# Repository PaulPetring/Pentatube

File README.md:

# Pentatube

144 leds filled with a new life

## Ongoing Documentation:

https://hackmd.c3d2.de/Pentatube

## Schematics

| Part         | Description | Datasheet |
|:------ |:----------- |:----------|
| XCVR1, XCVR2 | Differential Bus Transceiver | [SN65176B](http://www.ti.com/lit/ds/symlink/sn75176b.pdf) |
| SRR, SRG, SRB | 8-Bit Shift Register with Latch and Driver | [TPIC6595](http://www.ti.com/lit/ds/symlink/tpic6595.pdf) |
| uC    | ATMEL 8-Bit Microncontroller | [AT89C2051-24PU](https://ww1.microchip.com/downloads/en/DeviceDoc/doc0368.pdf) |
| MYC  | (probably) RGB LED  driver with PWM control. marked: JRC 6060 523 | [NJU6060](https://www.mouser.de/datasheet/2/294/NJU6060_E-52910.pdf) |

## Controller

)

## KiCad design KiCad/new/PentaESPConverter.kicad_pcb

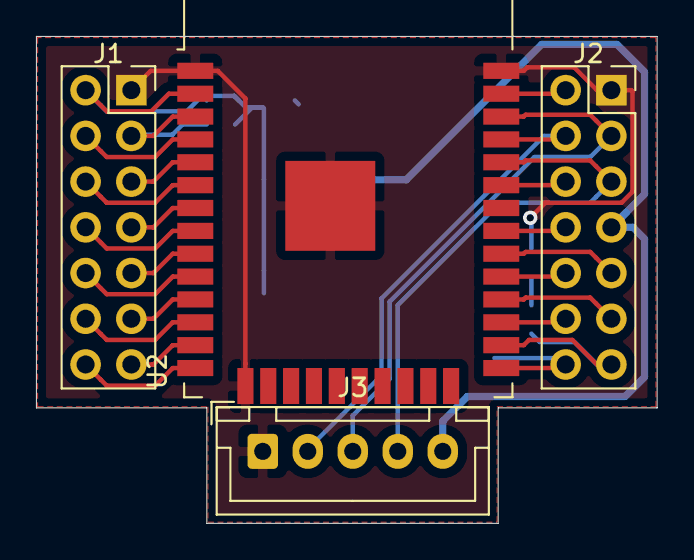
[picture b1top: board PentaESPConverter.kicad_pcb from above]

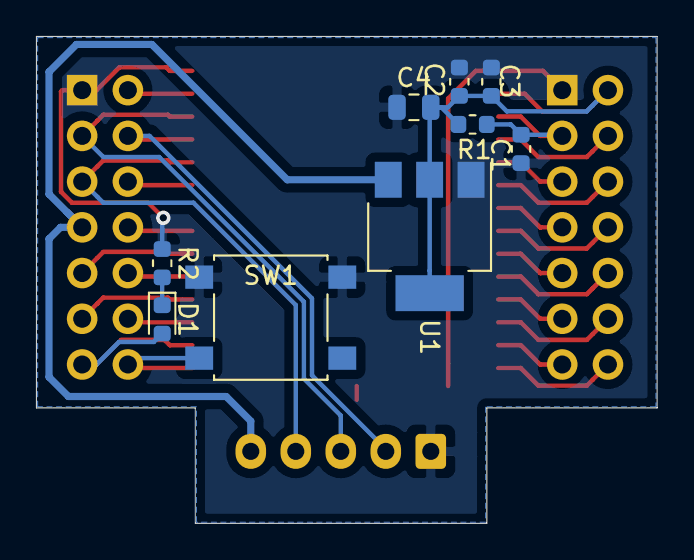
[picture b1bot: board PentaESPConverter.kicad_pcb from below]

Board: 2 copper layers, 34.5 x 27.1 mm, 13 parts (9 on the bottom side), 28 nets.

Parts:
C1, C3: 0.1uF; C_0603_1608Metric
C2: 10uF; C_0603_1608Metric
C4: 22uF; C_0805_2012Metric
D1: LED; LED_0603_1608Metric
J1, J2: Conn_02x07_Odd_Even; PinSocket_2x07_P2.54mm_Vertical
J3: Conn_01x05; JST_XH_B05B-XH-A_1x05_P2.50mm_Vertical
R1: 10K; R_0603_1608Metric
R2: R; R_0603_1608Metric
SW1: SW_Push; SW_SPST_B3S-1000
U1: AMS1117-3.3; SOT-223-3_TabPin2
U2: ESP32-WROOM-32

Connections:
+3V3: C2.2, C3.2, C4.2, J1.2, R1.1, U1.2, U2.2
+5V: J2.7, J3.5, U1.3
GND: C1.2, C2.1, C3.1, C4.1, J1.1, J2.1, J3.1, R2.1, SW1.2, U1.1, U2.1, U2.15, U2.38, U2.39
JST2: J2.4, J3.2, U2.35
JST3: J2.3, J3.3, U2.36
JST4: J2.5, J3.4, U2.34
unnamed: D1.1, R2.2
P3: C1.1, J1.3, R1.2, U2.3
P4: J1.4, U2.4
P5: J1.5, U2.5
P6: J1.6, U2.6
P7: J1.7, U2.7
P8: J1.8, U2.8
P9: J1.9, U2.9
P10: J1.10, U2.10
P11: J1.11, U2.11
P12: J1.12, U2.12
P13: J1.13, U2.13
P14: J1.14, U2.14
P25: J2.14, SW1.1, U2.25
P26: D1.2, J2.13, U2.26
P27: J2.12, U2.27
P28: J2.11, U2.28
P29: J2.10, U2.29
P30: J2.9, U2.30
P31: J2.8, U2.31
P33: J2.6, U2.33
P37: J2.2, U2.37

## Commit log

2019-03-06 init
2019-03-06 added pictures to README
2019-03-12 Artnet, minimal controller
2019-04-16 added v1.0 of converter board
2019-06-03 added arduino library incl. Artnet and Strandtest example
2019-06-11 add MatePlate files
2019-06-12 added current PCB Design
2019-06-12 added multicore multiwifi and some artnet adjustments
2019-06-12 update the new footprint of the board in FreeCad
2019-06-12 add paste stencil for soldering bottom of controller board
2019-06-18 adjust MatePlate for manufacturing tolerances
    - move ESP32 board 0.15mm in y-direction as this was the
    observed misalignment
    - add cutouts on antenna edge of ESP32 as there where small
    burrs left from manufacturing
2019-08-23 camp2019
2019-08-23 cleanup
